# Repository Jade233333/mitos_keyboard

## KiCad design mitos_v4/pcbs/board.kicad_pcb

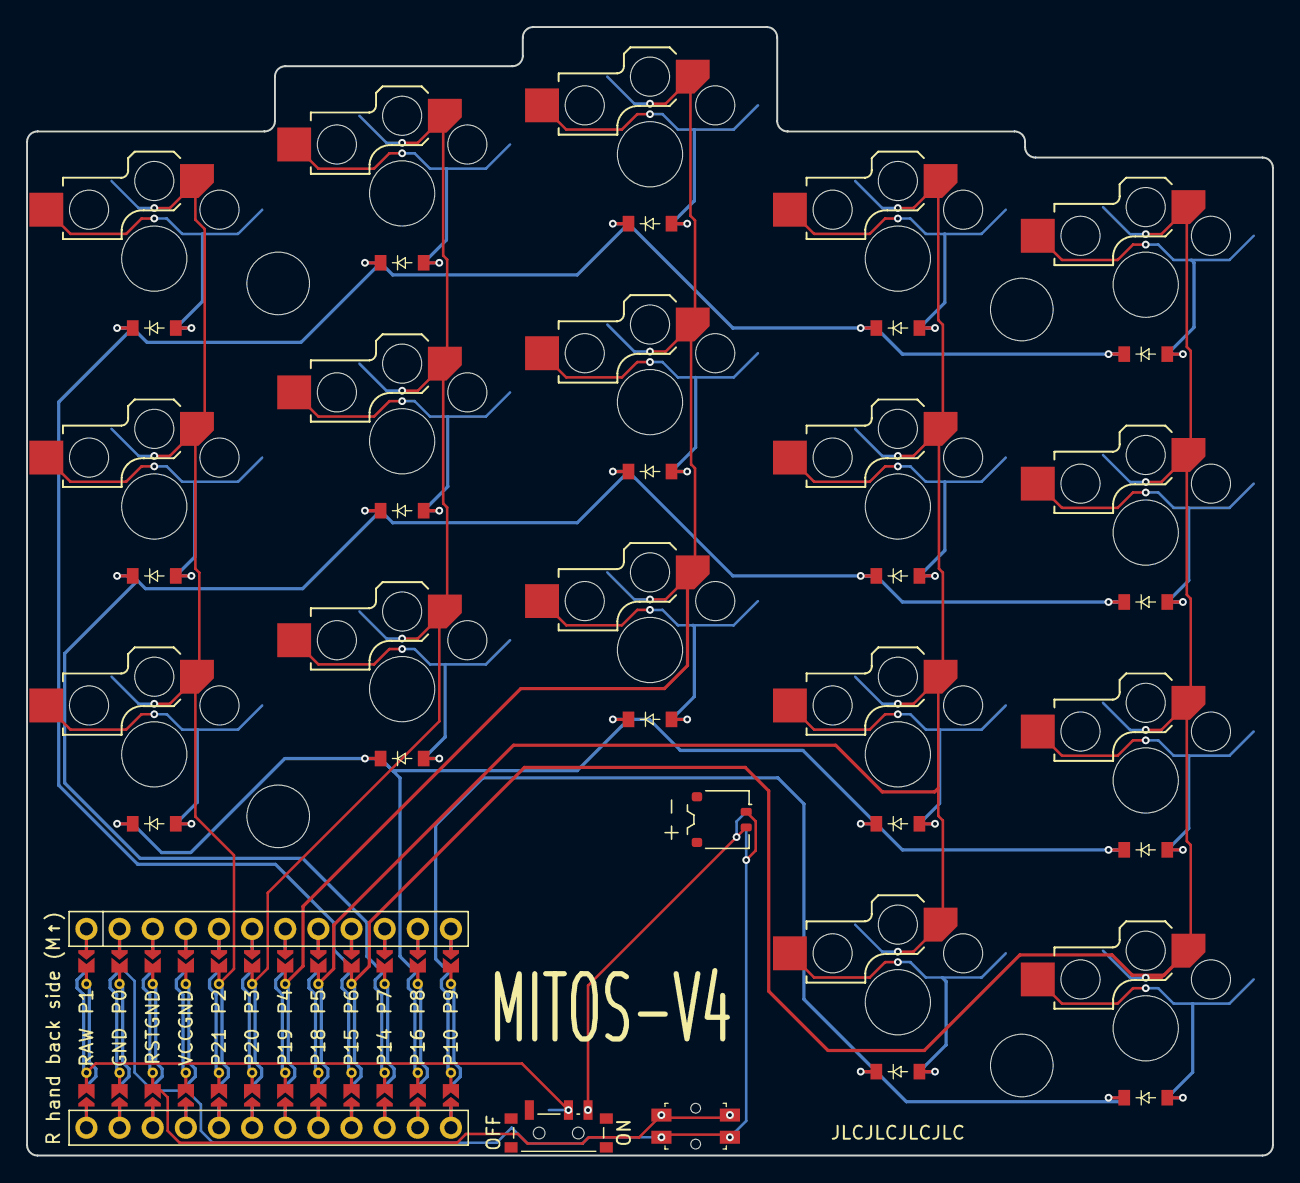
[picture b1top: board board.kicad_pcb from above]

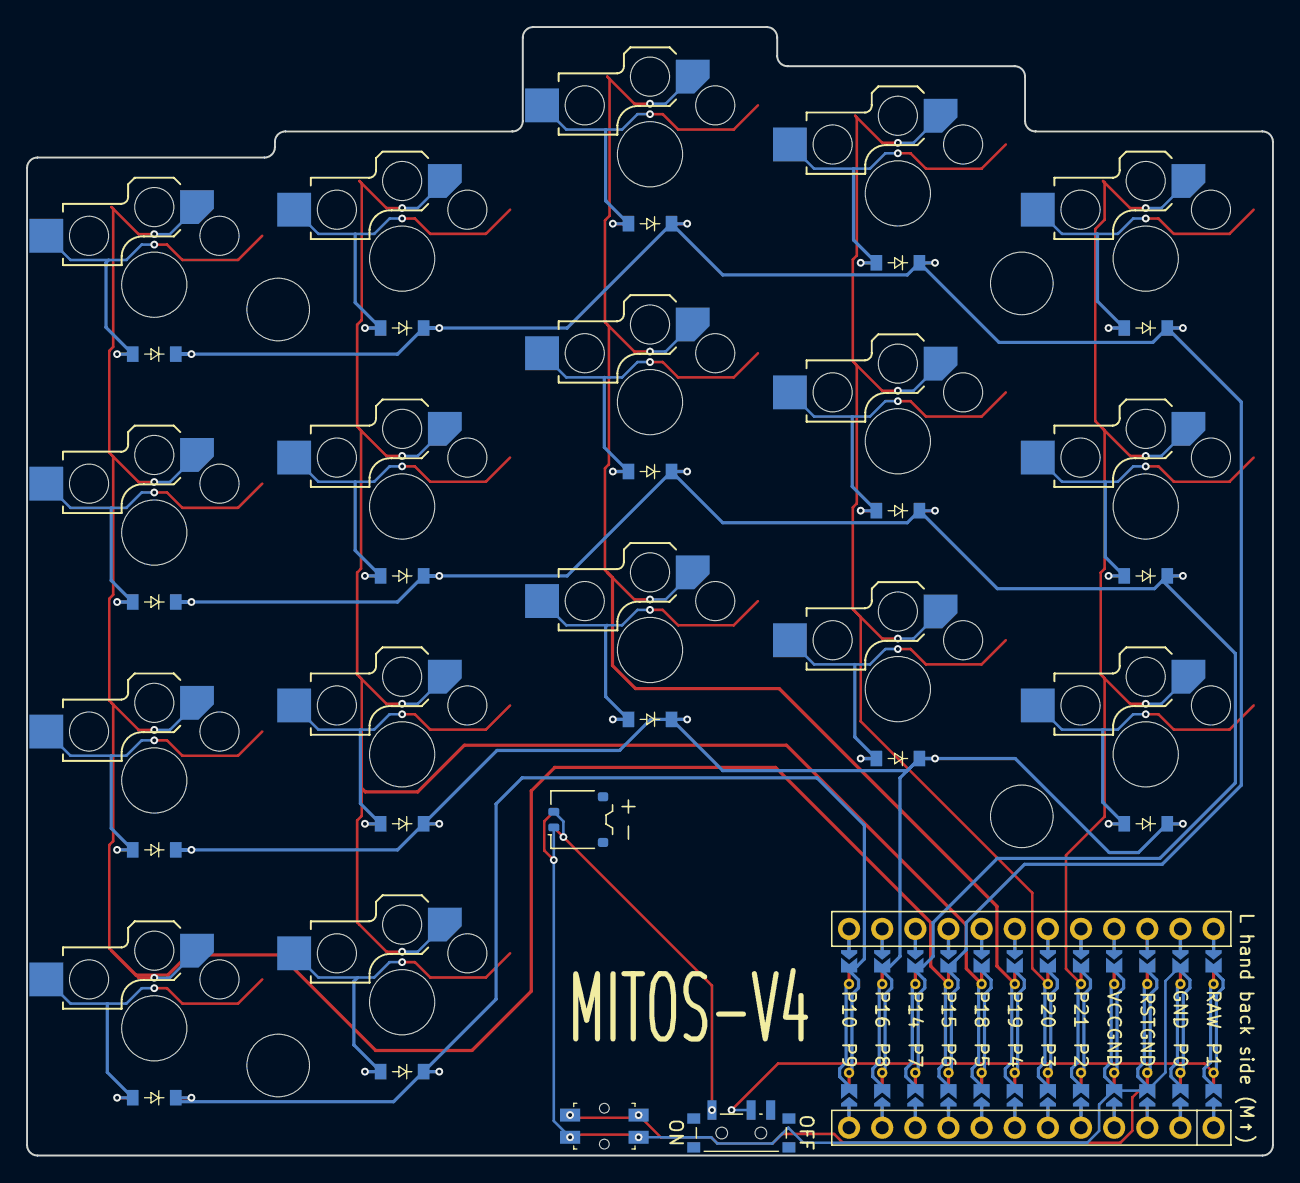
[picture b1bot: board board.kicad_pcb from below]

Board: 2 copper layers, 95.5 x 86.5 mm, 42 parts (17 on the bottom side), 30 nets.

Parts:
CONN1: battery_connector_molex_pico_ezmate_1x02
D1, D2, D3, D4, D5, D6, D7, D8, D9, D10, D11, D12, D13, D14, D15, D16, D17: diode_tht_sod123
MCU1: mcu_supermini_nrf52840
MH1, MH2, MH3, MH4: mounting_hole_npth
PWR1: power_switch_smd_side
RST1: reset_switch_smd_side
S1, S2, S3, S4, S5, S6, S7, S8, S9, S10, S11, S12, S13, S14, S15, S16, S17: switch_choc_v1_v2

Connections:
BAT_P: CONN1.2, PWR1.1, PWR1.3
GND: CONN1.1, MCU1.103, MCU1.104, MCU1.123, RST1.1, RST1.3
P2: MCU1.105, S1.1, S2.1, S3.1
P3: MCU1.106, S4.1, S5.1, S6.1
P4: MCU1.107, S7.1, S8.1, S9.1
P5: MCU1.108, S10.1, S11.1, S12.1, S13.1
P6: MCU1.109, S14.1, S15.1, S16.1, S17.1
P10: D10.1, D14.1, MCU1.113
P14: D2.1, D5.1, D8.1, D12.1, D16.1, MCU1.115
P15: D3.1, D6.1, D9.1, D13.1, D17.1, MCU1.116
P16: D1.1, D4.1, D7.1, D11.1, D15.1, MCU1.114
RAW: MCU1.124, PWR1.2
RST: MCU1.122, RST1.2, RST1.4
index_bottom: D11.2, S11.2
index_home: D12.2, S12.2
index_thumb: D10.2, S10.2
index_top: D13.2, S13.2
inner_bottom: D15.2, S15.2
inner_home: D16.2, S16.2
inner_thumb: D14.2, S14.2
inner_top: D17.2, S17.2
middle_bottom: D7.2, S7.2
middle_home: D8.2, S8.2
middle_top: D9.2, S9.2
pinky_bottom: D1.2, S1.2
pinky_home: D2.2, S2.2
pinky_top: D3.2, S3.2
ring_bottom: D4.2, S4.2
ring_home: D5.2, S5.2
ring_top: D6.2, S6.2

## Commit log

2024-07-30 yaml
2024-07-31 end of day 2
2024-08-06 new keyboard
2024-08-10 fillet
2024-08-14 new footprint
2024-08-16 final
2024-08-16 Revert "final"
    This reverts commit 3cc0ae3dbf9a7bfc7c0c773b724c9739fb3c472e.
2024-08-16 silkscreen
2024-08-16 archive gbr
2024-08-17 update file sturecture, add jlcnumber
2024-08-17 gitignore
2024-08-31 padding adjust
2024-08-31 19mm update
2024-08-31 jlc mk2 update
2024-08-31 gbr move location
2024-09-15 plate update and slim version
2024-09-19 mk12 config
2024-09-22 mk3 pcb donw
2024-12-15 battery connector change
2025-03-14 Create LICENSE
2025-04-02 update footprint
2025-04-02 update footprint usage, and mounting hole position and use choc switch
2025-04-03 add wirehole for external antenna
2025-04-03 draft pcb done
2025-04-04 remove mounting hole, use top instead
2025-04-04 config file for v3
2025-04-04 folder for v3
2025-04-04 add gbr
2025-04-04 remove mk3
2025-04-04 ignore output folder
2025-04-05 add mounting hole for bottom mount
2025-04-06 the real v3
2025-04-06 clean up v3
2025-04-09 remove support for the choc v1 and pad for stabolizer
2025-04-15 update plate bottom lineup
2025-04-16 config update
2025-04-16 add 3d model for pcb
2025-04-16 use pkxy as unit
2025-04-16 remove cases part
2025-04-16 mounting hole size change 5-3.8
2025-04-17 add v4
2025-04-19 update 3d file
2025-04-19 version 4 donw
2025-04-19 add kicad pcb file
2025-04-25 clean up for v4
2025-04-30 remove plate and case model from root
